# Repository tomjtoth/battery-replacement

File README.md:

# 3.9V battery replacement

I'd like to replace Li-ion cells from the battery package of mobile devices
with this DC DC converter, which shall step 5V received from any USB port/charger down to 3.9V.

## Conflict with charging via USB port

The devices USB port should not be used for charging after this integration.
Special cables (with unconnected VBUS) should be used when connecting to computers.

## Design choices

At 5V3A - a type-C DFP can provide without active negotiation - the _ideal_ power budget is 15W.
That should translate to about 3.84A at 3.9V.

As a worst case scenario I picked the largest transient as 3.8A and V_IN as 4.5V.
Using the converter's formulas I got 272.6mV sag and 12.7mV soar on the output.

My calculations and links to datasheets can be found
[here](https://docs.google.com/spreadsheets/d/1-LQr6ypT5iOjkNXZSsbeC3mkMsgCNXlFd2zotSDCdQk/edit?usp=sharing).

I'd like to produce this via JLCPCB, so I'm using only their components. All components are imported via JLCImport.
I minimized extended component usage, but I'm happy to pay extra for the 549k resistor, to keep the footprint smaller.

### RT5788B converter

Has 7V absolute maximum input voltage and 100% maximum duty cycle, can provide 4A continuously.
I'm not using the PGOOD leg of the converter to save space.

I found 2 revisions of its datasheet and proceeded with the earlier one where C_OUT = 2 x 22uF (vs 3 x 22uF on the newer revision).
C_IN is 22uF which exceeds the 10uF allowed by USB standard on Upward Facing Ports.

### Y4203 load switch

The 250us soft-start allows the above mentioned 22uF C_IN to be charged.
Has 6.1V OVP with 50ns response time.

## Schematics

I tried arranging the converter's pins similarly to as seen in the datasheet's Typical Application Circuit.

## PCB

The board is 9 x 25mm sized. The minimum 5 pieces of 100x100mm panels (at JLCPCB) should yield 5x10x4 pieces
(leaving 2x5mm strips on 2 sides for manufacturing holes).
I'm using copper pours for GND on both sides.
I placed vias under the converter in hopes of driving heat to the undivided bottom Cu plane.

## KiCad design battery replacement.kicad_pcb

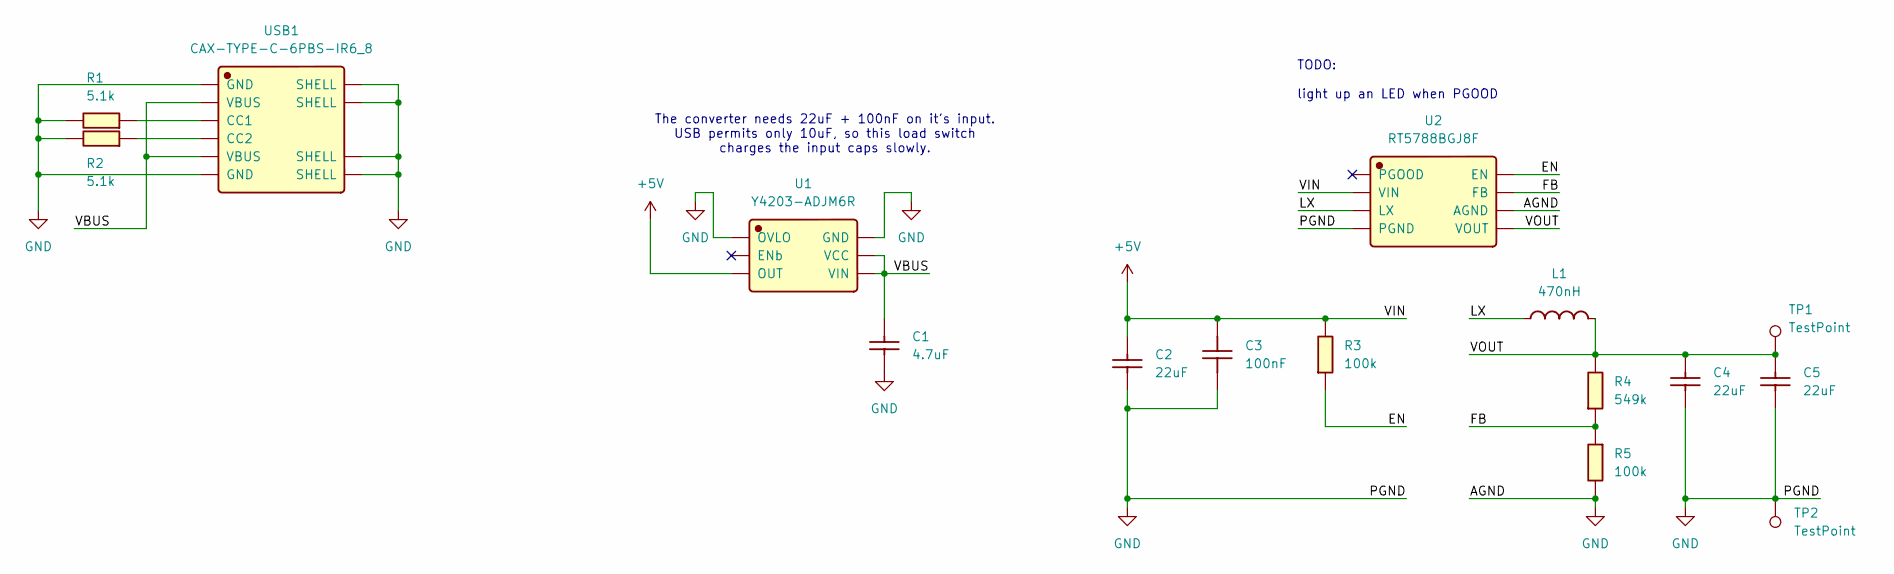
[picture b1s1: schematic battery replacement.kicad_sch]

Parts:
C1: 4.7uF; CL21A475KAQNNNE; Manufacturer Part CL21A475KAQNNNE; LCSC C1779
C2, C4, C5: 22uF; CL31A226KAHNNNE; Manufacturer Part CL31A226KAHNNNE; LCSC C12891
C3: 100nF; CL05B104KB54PNC; Manufacturer Part CL05B104KB54PNC; LCSC C307331
L1: 470nH; TMS252012ALM-R47MTAA; Manufacturer Part TMS252012ALM-R47MTAA; LCSC C24296304
R1, R2: 5.1k; 0402WGF5101TCE; Manufacturer Part 0402WGF5101TCE; LCSC C25905
R3, R5: 100k; 0402WGF1003TCE; Manufacturer Part 0402WGF1003TCE; LCSC C25741
R4: 549k; 0402WGF5493TCE; Manufacturer Part 0402WGF5493TCE; LCSC C25795
TP1, TP2: TestPoint; TestPoint_THTPad_D1.0mm_Drill0.5mm
U1: Y4203-ADJM6R; Manufacturer Part Y4203-ADJM6R; LCSC C49270370
U2: RT5788BGJ8F; Manufacturer Part RT5788BGJ8F; LCSC C3194337
USB1: CAX-TYPE-C-6PBS-IR6_8; Manufacturer Part CAX-TYPE-C-6PBS-IR6.8; LCSC C55072612

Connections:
+5V: C2.2, C3.1, R3.2, U1.3 (OUT), U2.2 (VIN)
/EN: R3.1, U2.8 (EN)
/FB: R4.1, R5.1, U2.7 (FB)
/LX: L1.1, U2.3 (LX)
/VBUS: C1.2, U1.4 (VIN), U1.5 (VCC), USB1.A9 (VBUS), USB1.B9 (VBUS)
/VOUT: C4.2, C5.2, L1.2, R4.2, TP1.1 (1_1), U2.5 (VOUT)
GND: C1.1, C2.1, C3.2, C4.1, C5.1, R1.2, R2.2, R5.2, TP2.1 (1_1), U1.1 (OVLO), U1.6 (GND), U2.4 (PGND), U2.6 (AGND), USB1.1 (SHELL), USB1.2 (SHELL), USB1.3 (SHELL), USB1.4 (SHELL), USB1.A12 (GND), USB1.B12 (GND)
unnamed: R1.1, USB1.A5 (CC1)
unnamed: R2.1, USB1.B5 (CC2)

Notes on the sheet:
TODO: light up an LED when PGOOD
The converter needs 22uF + 100nF on it's input. USB permits only 10uF, so this load switch charges the input caps slowly.

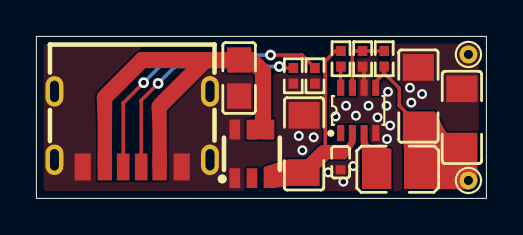
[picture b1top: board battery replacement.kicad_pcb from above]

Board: 2 copper layers, 25.0 x 9.0 mm, 16 parts (0 on the bottom side), 9 nets.
